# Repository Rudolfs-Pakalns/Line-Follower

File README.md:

# Line Follower

## This project contains code and resources for a line-following robot.

## Contents
- STM32 code for line-following robot
- KiCad schematic and PCB design files
- 3D model of the robot chassis
- Bill of Materials (BOM) for components used

[Line Follower Rules](https://robotuskola.lv/wp-content/uploads/2025/10/linefollower-rules-lv.pdf)

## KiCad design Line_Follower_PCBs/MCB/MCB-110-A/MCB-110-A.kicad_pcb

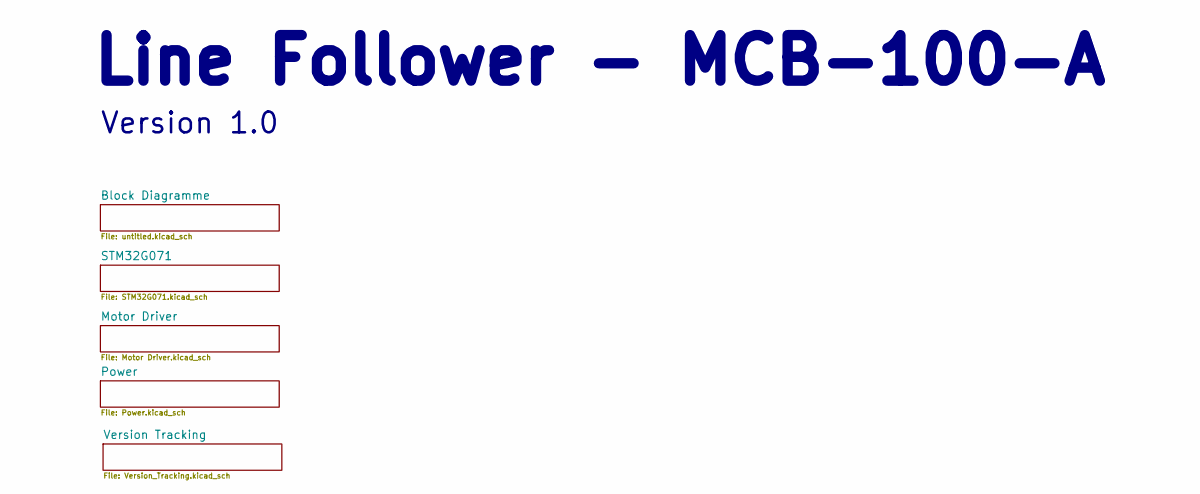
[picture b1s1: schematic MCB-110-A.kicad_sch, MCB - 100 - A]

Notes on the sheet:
Line Follower - MCB-100-A
Version 1.0

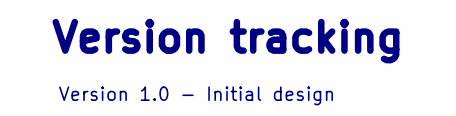
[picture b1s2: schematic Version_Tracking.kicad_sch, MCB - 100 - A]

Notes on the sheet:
Version 1.0 - Initial design
Version tracking

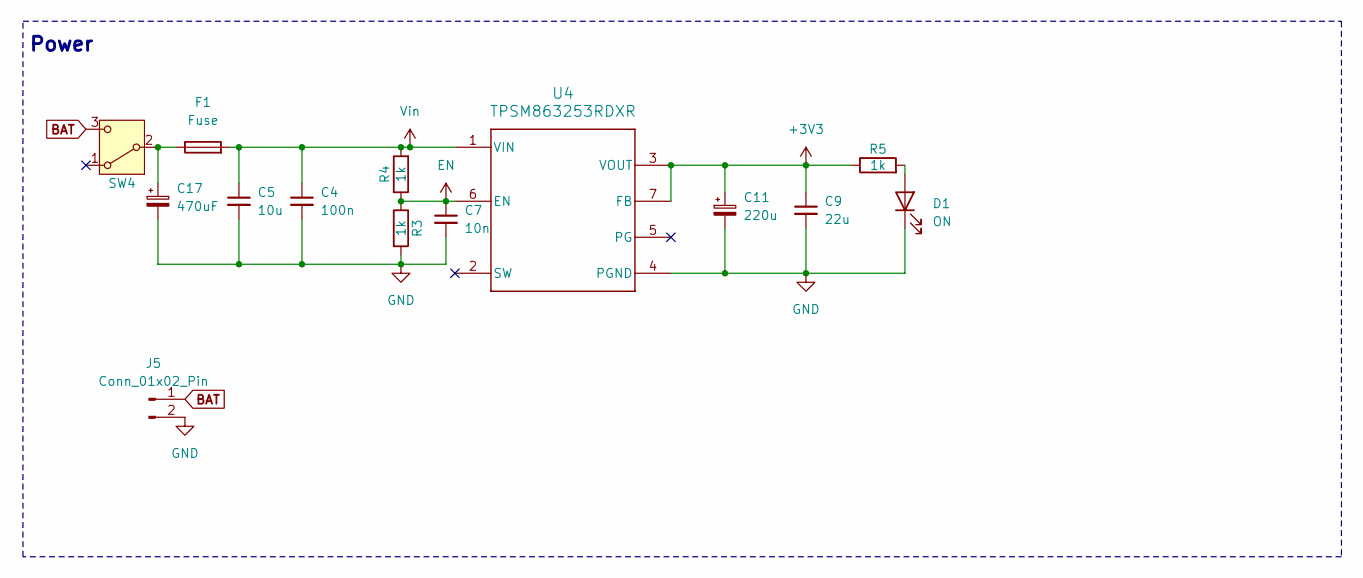
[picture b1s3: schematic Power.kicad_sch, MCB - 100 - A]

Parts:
C4: 100n; C_0805_2012Metric_Pad1.18x1.45mm_HandSolder
C5: 10u; C_0805_2012Metric_Pad1.18x1.45mm_HandSolder
C7: 10n; C_0805_2012Metric_Pad1.18x1.45mm_HandSolder
C9: 22u; C_0805_2012Metric_Pad1.18x1.45mm_HandSolder
C11: 220u; CP_Elec_8x10.5
C17: 470uF; CP_Elec_8x10.5
D1: ON; LED_1206_3216Metric
F1: Fuse; Fuse_Bourns_MF-RG300
J5: Conn_01x02_Pin; PinHeader_1x02_P2.54mm_Vertical
R3, R4, R5: 1k; R_0805_2012Metric_Pad1.20x1.40mm_HandSolder
SW4: SW_Nidec_CAS-120A1; SW_Slide_SPDT_Straight_CK_OS102011MS2Q
U4: TPSM863253RDXR; RDX0007A-MFG

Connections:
+3V3: C9.1, C11.1, R5.1, U4.3 (VOUT), U4.7 (FB); also elsewhere on the board
BAT: J5.1, SW4.3 (A); also elsewhere on the board
EN: C7.1, R3.1, R4.1, U4.6 (EN)
GND: C4.2, C5.2, C7.2, C9.2, C11.2, C17.2, D1.1 (K), J5.2, R3.2, U4.4 (PGND); also elsewhere on the board
unnamed: D1.2 (A), R5.2
unnamed: C17.1, F1.1, SW4.2 (B)
Vin: C4.1, C5.1, F1.2, R4.2, U4.1 (VIN)

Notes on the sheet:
Power

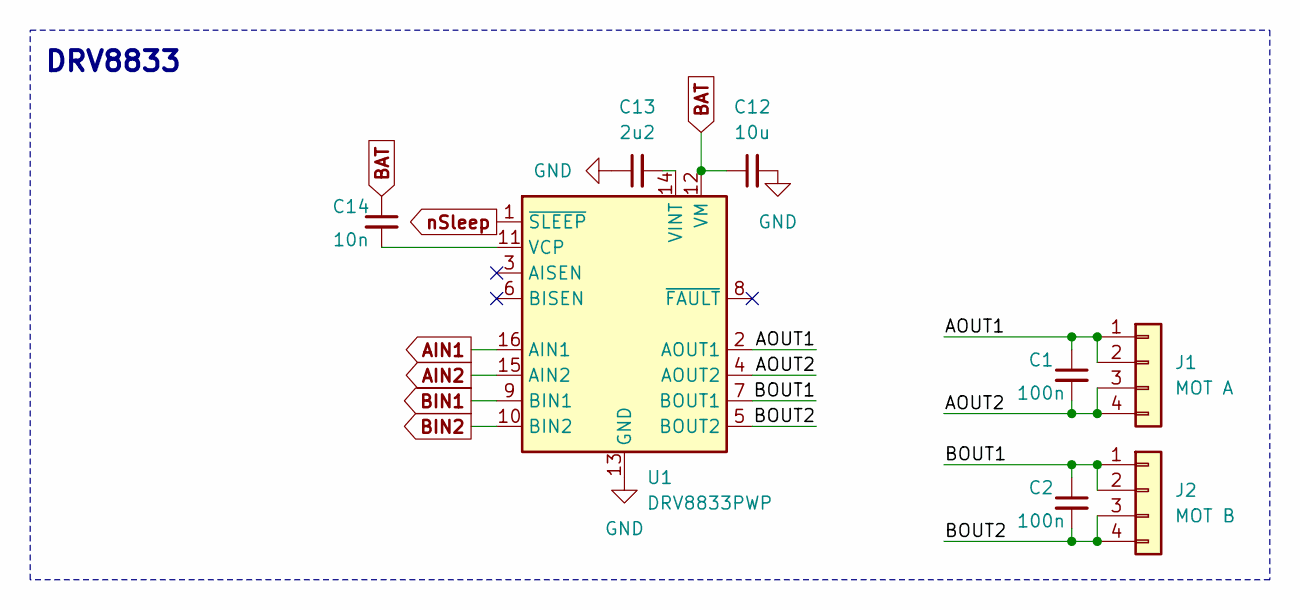
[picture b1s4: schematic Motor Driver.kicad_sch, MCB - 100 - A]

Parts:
C1, C2: 100n; C_0805_2012Metric_Pad1.18x1.45mm_HandSolder
C12: 10u; C_0805_2012Metric_Pad1.18x1.45mm_HandSolder
C13: 2u2; C_0805_2012Metric_Pad1.18x1.45mm_HandSolder
C14: 10n; C_0805_2012Metric_Pad1.18x1.45mm_HandSolder
J1: MOT A; PinHeader_1x04_P2.54mm_Vertical
J2: MOT B; PinHeader_1x04_P2.54mm_Vertical
U1: DRV8833PWP; HTSSOP-16-1EP_4.4x5mm_P0.65mm_EP3.4x5mm_Mask2.46x2.31mm_The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

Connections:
/Motor Driver/AOUT1: C1.1, J1.1, J1.2, U1.2 (AOUT1)
/Motor Driver/AOUT2: C1.2, J1.3, J1.4, U1.4 (AOUT2)
/Motor Driver/BOUT1: C2.1, J2.1, J2.2, U1.7 (BOUT1)
/Motor Driver/BOUT2: C2.2, J2.3, J2.4, U1.5 (BOUT2)
AIN1: U1.16 (AIN1); also elsewhere on the board
AIN2: U1.15 (AIN2); also elsewhere on the board
BAT: C12.1, C14.1, U1.12 (VM); also elsewhere on the board
BIN1: U1.9 (BIN1); also elsewhere on the board
BIN2: U1.10 (BIN2); also elsewhere on the board
GND: C12.2, C13.1, U1.13 (GND), U1.17 (GND); also elsewhere on the board
unnamed: C14.2, U1.11 (VCP)
unnamed: C13.2, U1.14 (VINT)
nSleep: U1.1 (~SLEEP); also elsewhere on the board

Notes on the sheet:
DRV8833

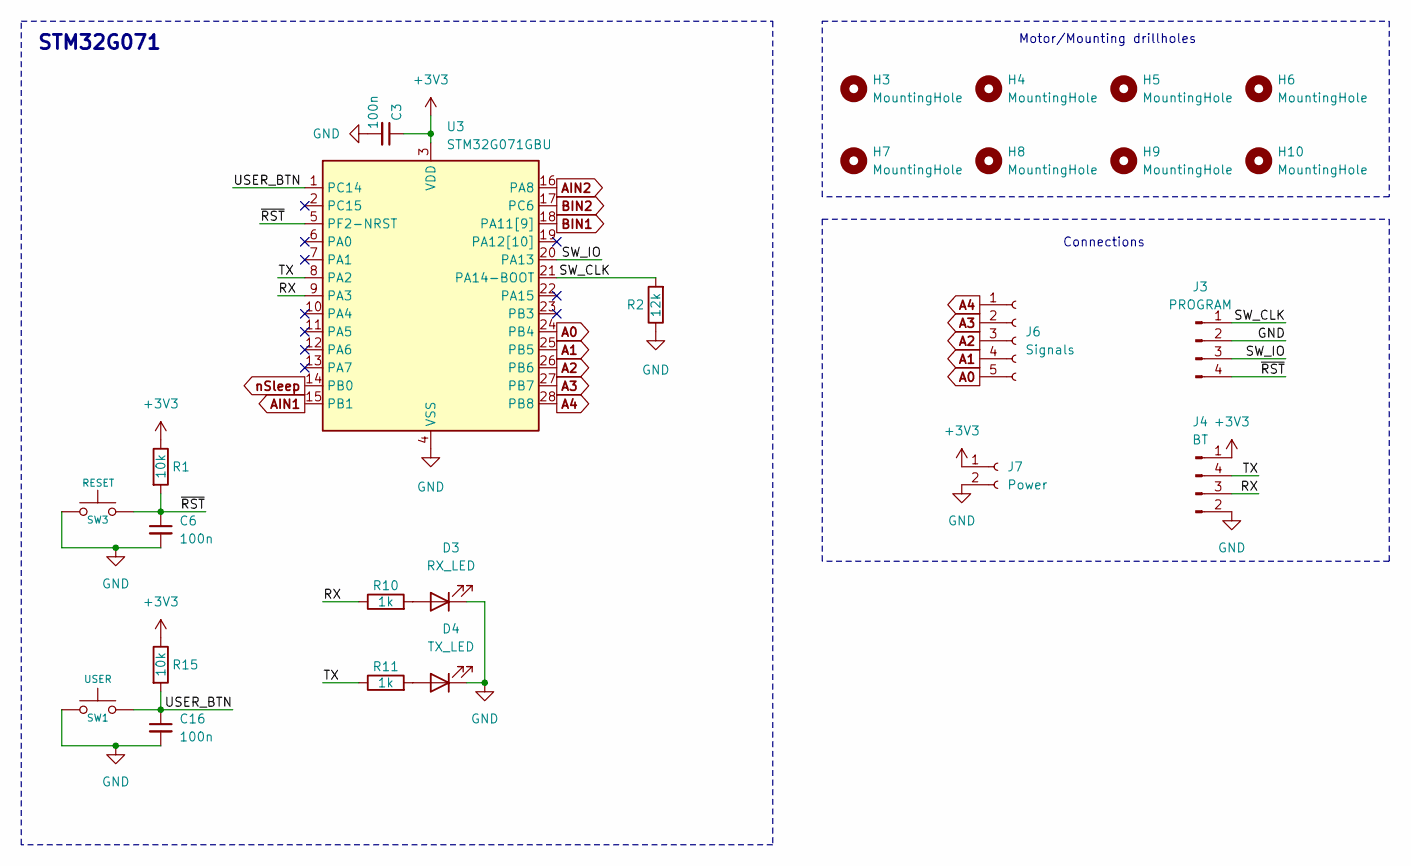
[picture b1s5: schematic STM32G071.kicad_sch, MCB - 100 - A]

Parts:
C3, C6, C16: 100n; C_0805_2012Metric_Pad1.18x1.45mm_HandSolder
D3: RX_LED; LED_1206_3216Metric
D4: TX_LED; LED_1206_3216Metric
H3, H4, H5, H6, H7, H8, H9, H10: MountingHole; MountingHole_3.2mm_M3
J3: PROGRAM; PinHeader_1x04_P2.54mm_Vertical
J4: BT; PinHeader_1x04_P2.54mm_Vertical
J6: Signals; JST_XH_B5B-XH-A_1x05_P2.50mm_Vertical
J7: Power; JST_XH_B2B-XH-A_1x02_P2.50mm_Vertical
R1, R15: 10k; R_0805_2012Metric_Pad1.20x1.40mm_HandSolder
R2: 12k; R_0805_2012Metric_Pad1.20x1.40mm_HandSolder
R10, R11: 1k; R_0805_2012Metric_Pad1.20x1.40mm_HandSolder
SW1: USER; SW_SPST_TL3305A
SW3: RESET; SW_SPST_TL3305A
U3: STM32G071GBU; QFN-28_4x4mm_P0.5mm

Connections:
+3V3: C3.1, J4.1, J7.1, R1.1, R15.1, U3.3 (VDD); also elsewhere on the board
/STM32G071/RX: J4.3, R10.1, U3.9 (PA3)
/STM32G071/SW_CLK: J3.1, R2.2, U3.21 (PA14-BOOT)
/STM32G071/SW_IO: J3.3, U3.20 (PA13)
/STM32G071/TX: J4.4, R11.1, U3.8 (PA2)
/STM32G071/USER_BTN: C16.1, R15.2, SW1.2, U3.1 (PC14)
/STM32G071/~RST: C6.1, J3.4 (Pin_2), R1.2, SW3.2, U3.5 (PF2-NRST)
A0: J6.5, U3.24 (PB4)
A1: J6.4, U3.25 (PB5)
A2: J6.3, U3.26 (PB6)
A3: J6.2, U3.27 (PB7)
A4: J6.1, U3.28 (PB8)
AIN1: U3.15 (PB1); also elsewhere on the board
AIN2: U3.16 (PA8); also elsewhere on the board
BIN1: U3.18 (PA11[9]); also elsewhere on the board
BIN2: U3.17 (PC6); also elsewhere on the board
GND: C3.2, C6.2, C16.2, D3.1 (K), D4.1 (K), J3.2 (Pin_4), J4.2, J7.2, R2.1, SW1.1, SW3.1, U3.4 (VSS); also elsewhere on the board
unnamed: D3.2 (A), R10.2
unnamed: D4.2 (A), R11.2
nSleep: U3.14 (PB0); also elsewhere on the board

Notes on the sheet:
Motor/Mounting drillholes
Connections
STM32G071

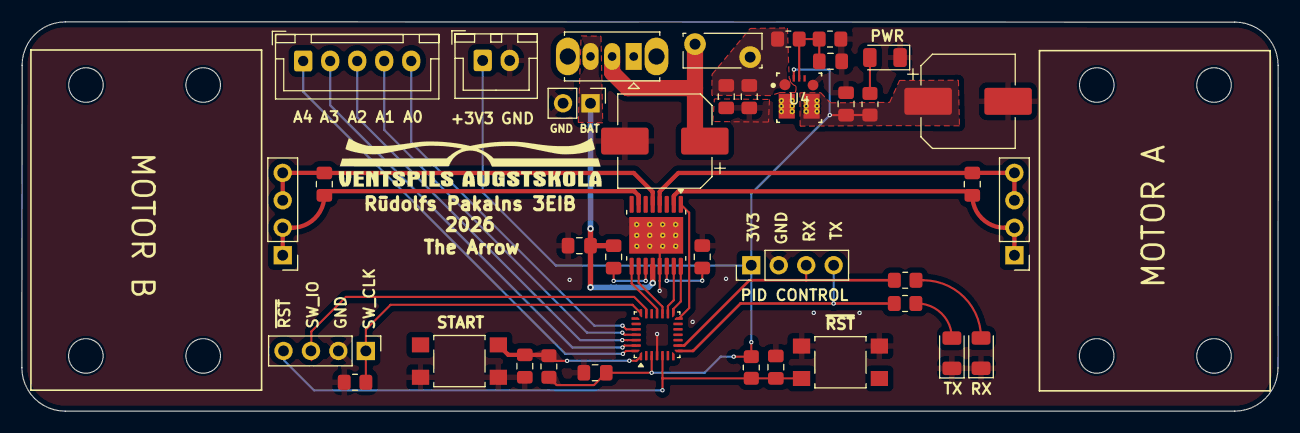
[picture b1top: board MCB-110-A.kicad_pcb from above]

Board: 2 copper layers, 116.2 x 36.0 mm, 47 parts (0 on the bottom side), 31 nets.

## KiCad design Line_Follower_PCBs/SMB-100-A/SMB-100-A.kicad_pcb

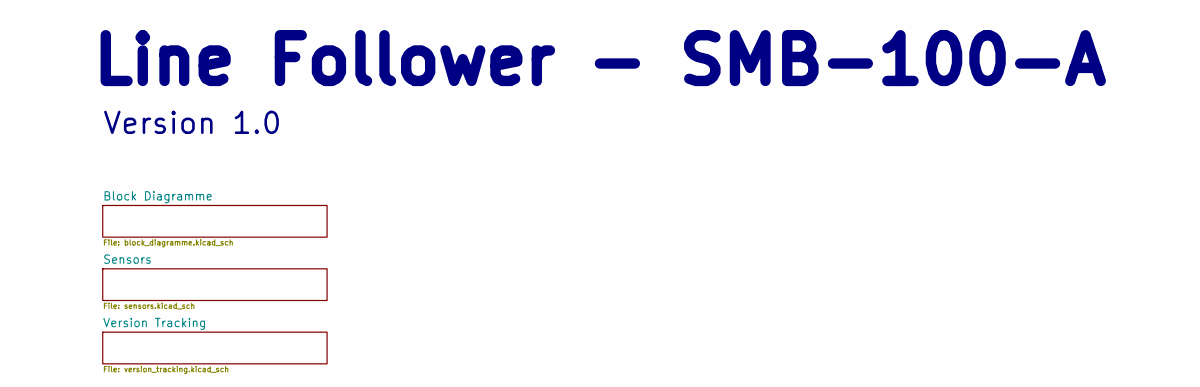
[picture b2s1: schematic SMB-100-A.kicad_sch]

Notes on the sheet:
Version 1.0
Line Follower - SMB-100-A

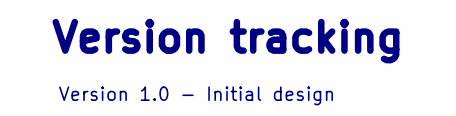
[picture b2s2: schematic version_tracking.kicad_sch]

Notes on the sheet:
Version 1.0 - Initial design
Version tracking

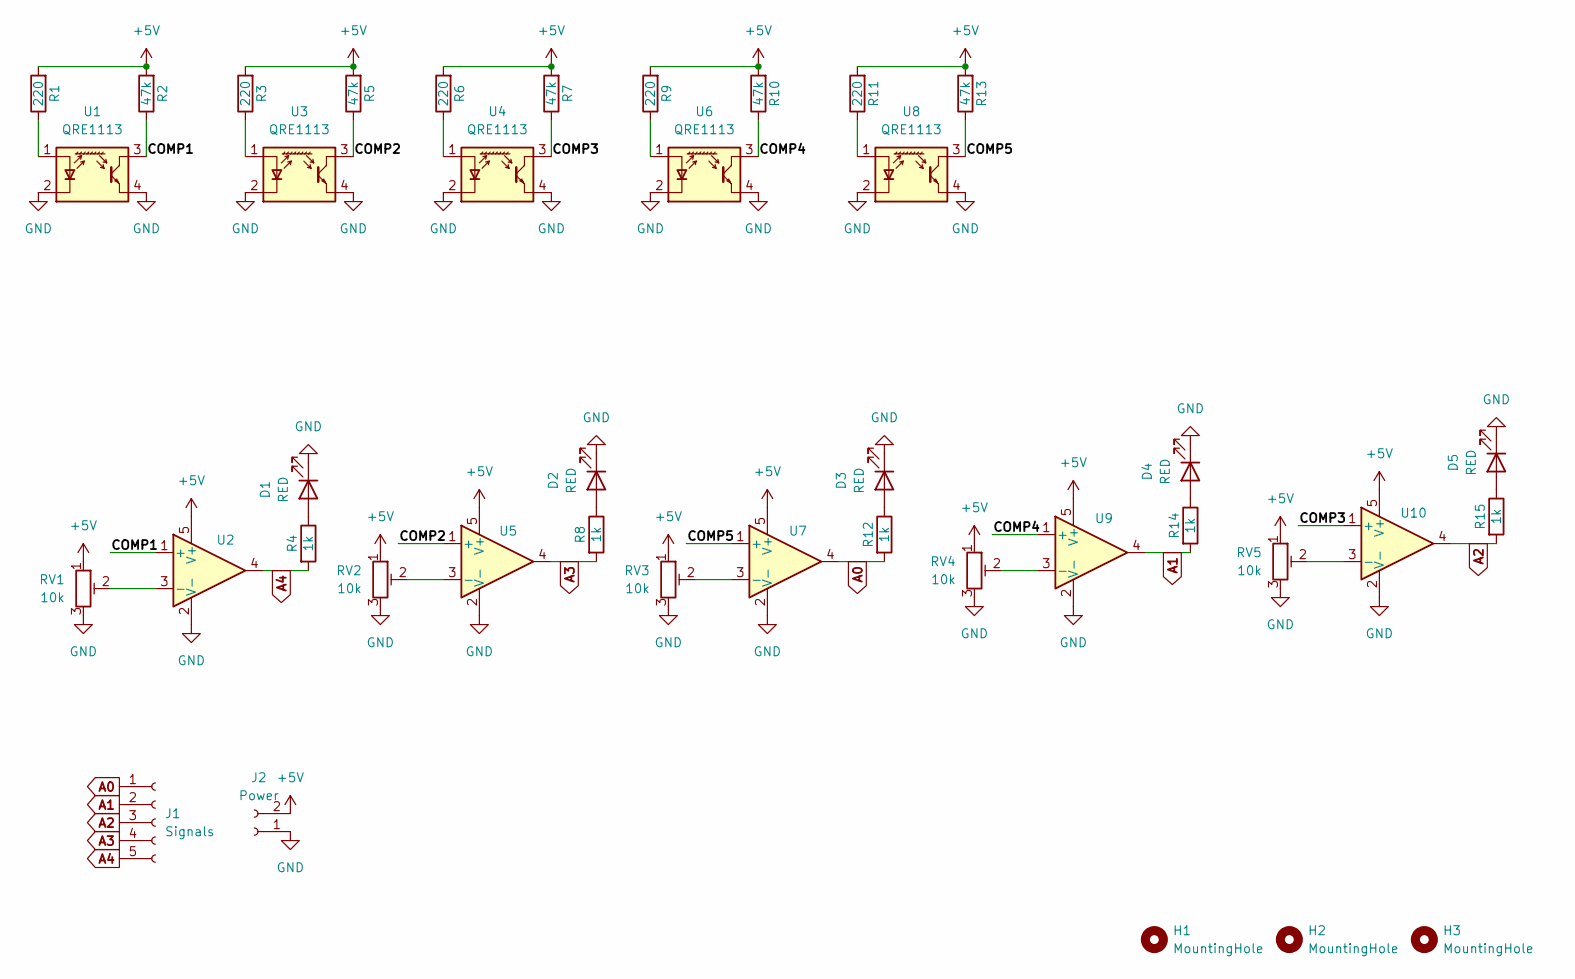
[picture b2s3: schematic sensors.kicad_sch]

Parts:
D1, D2, D3, D4, D5: RED; LED_1206_3216Metric
H1, H2, H3: MountingHole; MountingHole_3.2mm_M3
J1: Signals; JST_XH_B5B-XH-A_1x05_P2.50mm_Vertical
J2: Power; JST_XH_B2B-XH-A_1x02_P2.50mm_Vertical
R1, R3, R6, R9, R11: 220; R_0805_2012Metric_Pad1.20x1.40mm_HandSolder
R2, R5, R7, R10, R13: 47k; R_0805_2012Metric_Pad1.20x1.40mm_HandSolder
R4, R8, R12, R14, R15: 1k; R_0805_2012Metric_Pad1.20x1.40mm_HandSolder
RV1, RV2, RV3, RV4, RV5: 10k; Potentiometer_Bourns_TC33X_Vertical
U1, U3, U4, U6, U8: QRE1113; OnSemi_CASE100AQ
U2, U5, U7, U9, U10: MCP6001U; SOT-23-5_HandSoldering

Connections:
+3V3: J2.2, R1.2, R2.2, R3.2, R5.2, R6.2, R7.2, R9.2, R10.2, R11.2, R13.2, RV1.1, RV2.1, RV3.1, RV4.1, RV5.1, U2.5 (V+), U5.5 (V+), U7.5 (V+), U9.5 (V+), U10.5 (V+)
/Sensors/COMP1: R2.1, U1.3, U2.1 (+)
/Sensors/COMP2: R5.1, U3.3, U5.1 (+)
/Sensors/COMP3: R7.1, U4.3, U10.1 (+)
/Sensors/COMP4: R10.1, U6.3, U9.1 (+)
/Sensors/COMP5: R13.1, U7.1 (+), U8.3
A0: J1.1, R12.2, U7.4
A1: J1.2, R14.2, U9.4
A2: J1.3, R15.2, U10.4
A3: J1.4, R8.2, U5.4
A4: J1.5, R4.2, U2.4
GND: D1.1 (K), D2.1 (K), D3.1 (K), D4.1 (K), D5.1 (K), J2.1, RV1.3, RV2.3, RV3.3, RV4.3, RV5.3, U1.2 (K), U1.4, U2.2 (V-), U3.2 (K), U3.4, U4.2 (K), U4.4, U5.2 (V-), U6.2 (K), U6.4, U7.2 (V-), U8.2 (K), U8.4, U9.2 (V-), U10.2 (V-)
unnamed: D1.2 (A), R4.1
unnamed: D2.2 (A), R8.1
unnamed: D3.2 (A), R12.1
unnamed: D4.2 (A), R14.1
unnamed: D5.2 (A), R15.1
unnamed: R1.1, U1.1 (A)
unnamed: RV1.2, U2.3 (-)
unnamed: R3.1, U3.1 (A)
unnamed: R6.1, U4.1 (A)
unnamed: RV2.2, U5.3 (-)
unnamed: R9.1, U6.1 (A)
unnamed: RV3.2, U7.3 (-)
unnamed: R11.1, U8.1 (A)
unnamed: RV4.2, U9.3 (-)
unnamed: RV5.2, U10.3 (-)

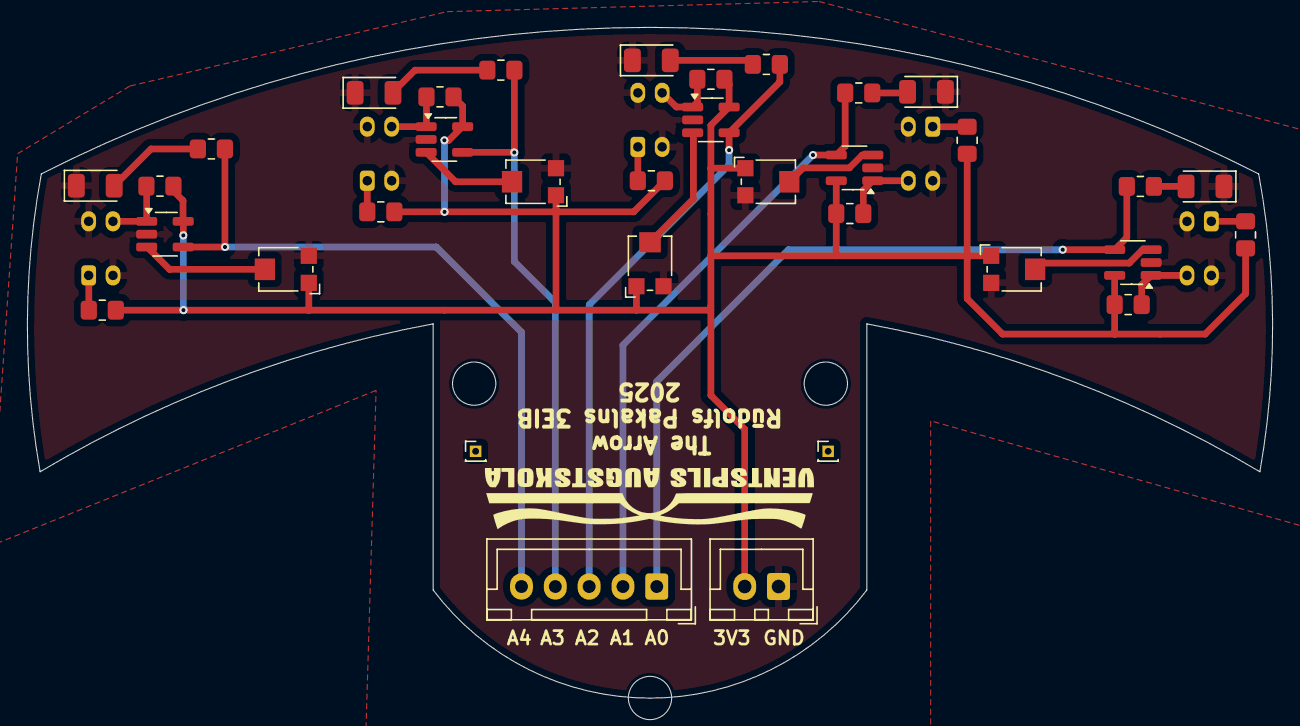
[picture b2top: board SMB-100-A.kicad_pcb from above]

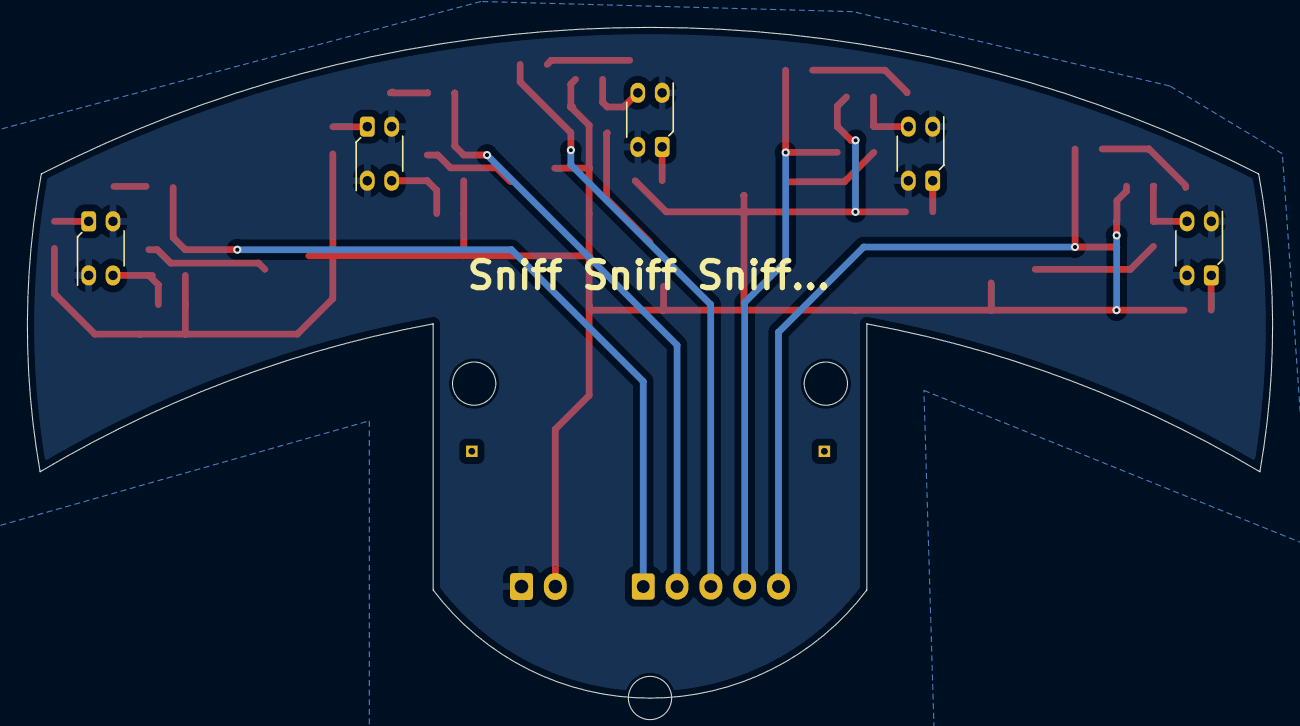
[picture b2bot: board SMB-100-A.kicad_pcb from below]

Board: 2 copper layers, 92.1 x 49.6 mm, 42 parts (5 on the bottom side), 27 nets.

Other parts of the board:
J3, J4: Conn_01x01_Pin; PinHeader_1x01_P1.00mm_Vertical

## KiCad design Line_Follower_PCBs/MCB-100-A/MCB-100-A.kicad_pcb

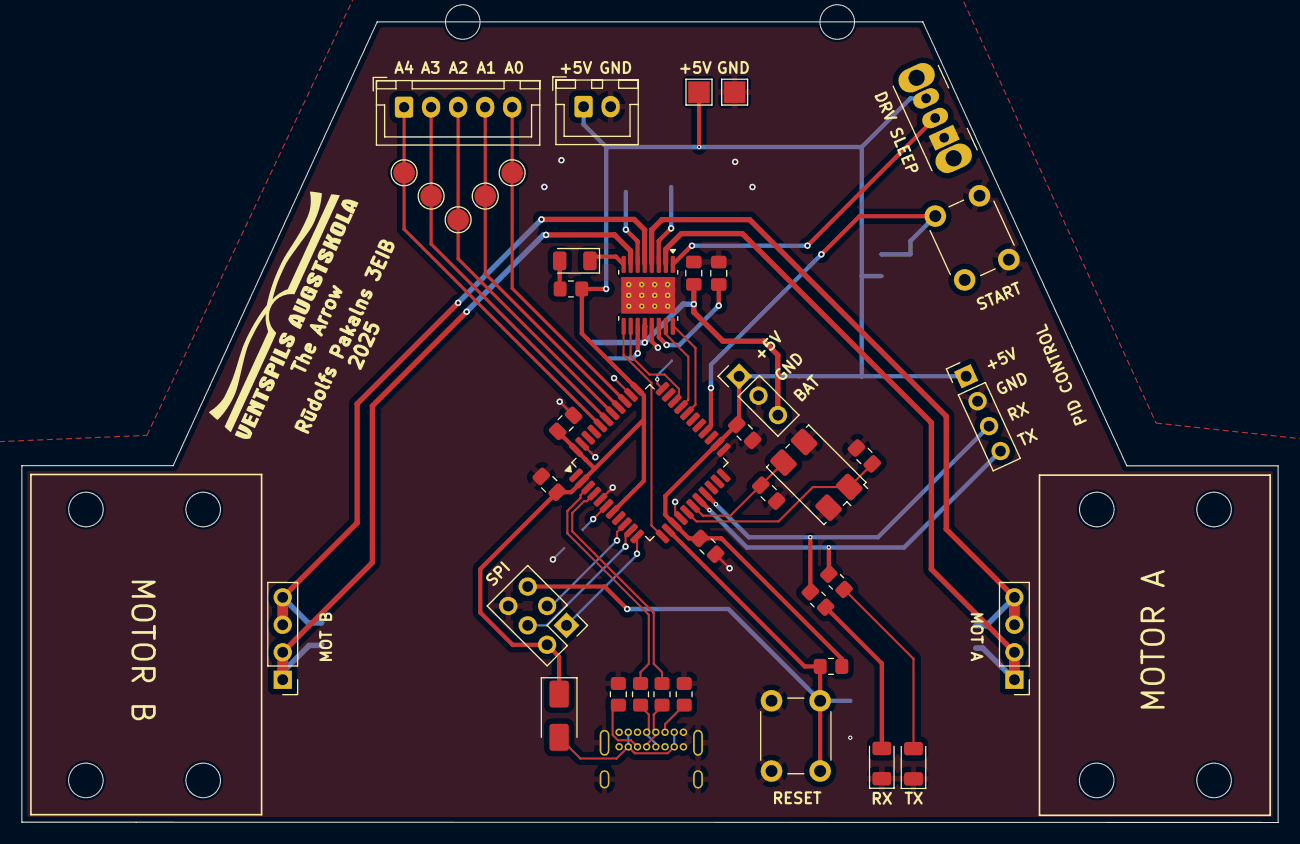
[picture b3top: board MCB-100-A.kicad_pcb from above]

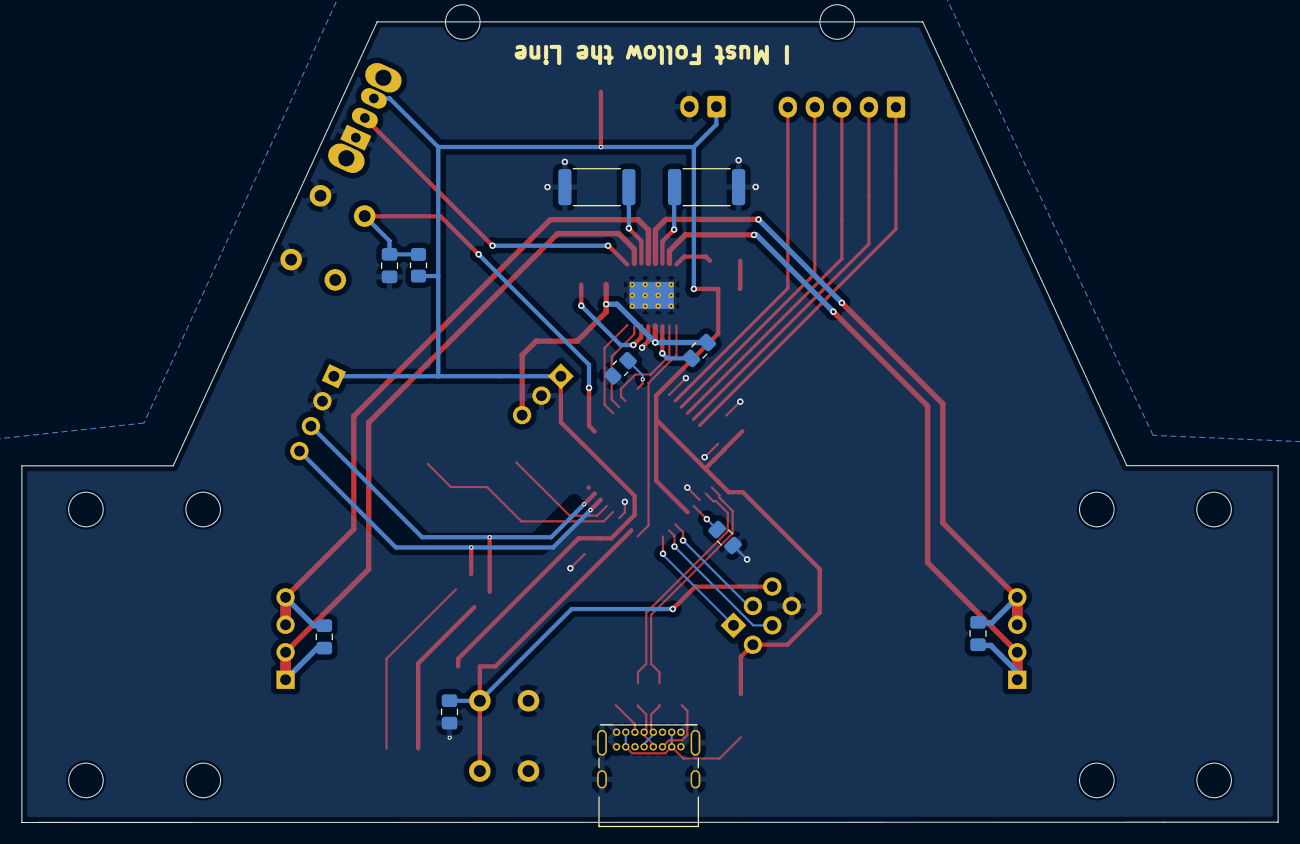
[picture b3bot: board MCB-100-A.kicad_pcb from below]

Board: 2 copper layers, 116.2 x 74.1 mm, 61 parts (11 on the bottom side), 43 nets.

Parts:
A1, A2, A3, A4, A5: TestPoint; TestPoint_Pad_D2.0mm
C1, C1#2, C2, C2#2, C3, C6, C15, C16: 100n; C_0805_2012Metric_Pad1.18x1.45mm_HandSolder
C4, C5: 20p; C_0805_2012Metric_Pad1.18x1.45mm_HandSolder
C7: 1u; C_0805_2012Metric_Pad1.18x1.45mm_HandSolder
C12: 10u; C_0805_2012Metric_Pad1.18x1.45mm_HandSolder
C13: 2u2; C_0805_2012Metric_Pad1.18x1.45mm_HandSolder
C14: 10n; C_0805_2012Metric_Pad1.18x1.45mm_HandSolder
D3: RX_LED; LED_1206_3216Metric
D4: TX_LED; LED_1206_3216Metric
D5: FAULT; LED_1206_3216Metric
D12: D_Schottky; D_SMA
H1, H2, H3, H4, H5, H6, H7, H8, H9, H10: MountingHole; MountingHole_3.2mm_M3
J1: MOT A; PinHeader_1x04_P2.54mm_Vertical
J2: MOT B; PinHeader_1x04_P2.54mm_Vertical
J3: USB_C_Receptacle_USB2.0_16P; USB_C_Receptacle_GCT_USB4085
J4: BT; PinHeader_1x04_P2.54mm_Vertical
J6: Signals; JST_XH_B5B-XH-A_1x05_P2.50mm_Vertical
J7: Power; JST_XH_B2B-XH-A_1x02_P2.50mm_Vertical
J9: Conn_01x03_Pin; PinHeader_1x03_P2.54mm_Vertical
J14: SPI; PinHeader_2x03_P2.54mm_Vertical
R1, R4, R15: 10k; R_0805_2012Metric_Pad1.20x1.40mm_HandSolder
R2, R3: 22; R_0805_2012Metric_Pad1.20x1.40mm_HandSolder
R10, R11, R12: 1k; R_0805_2012Metric_Pad1.20x1.40mm_HandSolder
R13, R14: 0.2; R_2512_6332Metric
R31, R32: 5k1; R_0805_2012Metric_Pad1.20x1.40mm_HandSolder
SW1: USER; SW_PUSH_6mm_H4.3mm
SW2: Sl_En; SW_Slide_SPDT_Angled_CK_OS102011MA1Q
SW3: RESET; SW_PUSH_6mm_H4.3mm
TP9, TP10: TestPoint; TestPoint_Pad_2.0x2.0mm
U1: DRV8833PWP; HTSSOP-16-1EP_4.4x5mm_P0.65mm_EP3.4x5mm_Mask2.46x2.31mm_The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
U2: ATmega32U4-A; TQFP-44_10x10mm_P0.8mm
Y1: Crystal_GND24; Crystal_SMD_FOX_FQ7050-4Pin_7.0x5.0mm

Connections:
+5V: C1.1, C2.1, C3.1, C15.1, D12.1 (K), J4.1, J7.1, J9.1, J14.2, R1.1, R12.2, R15.1, SW2.3 (A), TP9.1, U2.2 (UVCC), U2.7 (VBUS), U2.14 (VCC), U2.24 (AVCC), U2.34 (VCC), U2.44 (AVCC)
/ATmega32u4/D1+: J3.A6 (D+), J3.B6 (D+), R2.2
/ATmega32u4/D1-: J3.A7 (D-), J3.B7 (D-), R3.1
/ATmega32u4/D+: R2.1, U2.4 (D+)
/ATmega32u4/D-: R3.2, U2.3 (D-)
/ATmega32u4/MISO: J14.1, U2.11 (PB3)
/ATmega32u4/MOSI: J14.4, U2.10 (PB2)
/ATmega32u4/RESET: C6.1, J14.5, R1.2, SW3.2, U2.13 (~RESET)
/ATmega32u4/RX: J4.3, R10.1, U2.19 (PD1)
/ATmega32u4/SCK: J14.3, U2.9 (PB1)
/ATmega32u4/TX: J4.4, R11.1, U2.18 (PD0)
/ATmega32u4/USER_BTN: C16.1, R15.2, SW1.2, U2.26 (PD6)
/ATmega32u4/XTAL1: C5.1, U2.17 (XTAL1), Y1.3
/ATmega32u4/XTAL2: C4.1, U2.16 (XTAL2), Y1.1
/Motor Driver/AOUT1: C1#2.1, J1.1, J1.2, U1.2 (AOUT1)
/Motor Driver/AOUT2: C1#2.2, J1.3, J1.4, U1.4 (AOUT2)
/Motor Driver/ASEN: R13.1, U1.3 (AISEN)
/Motor Driver/BOUT1: C2#2.1, J2.1, J2.2, U1.7 (BOUT1)
/Motor Driver/BOUT2: C2#2.2, J2.3, J2.4, U1.5 (BOUT2)
/Motor Driver/BSEN: R14.1, U1.6 (BISEN)
/Motor Driver/Sleep: SW2.2 (B), U1.1 (~SLEEP)
A0: A4.1, J6.5, U2.36 (PF7)
A1: A3.1, J6.4, U2.37 (PF6)
A2: A5.1, J6.3, U2.38 (PF5)
A3: A2.1, J6.2, U2.39 (PF4)
A4: A1.1, J6.1, U2.40 (PF1)
BAT: C12.1, C14.1, J9.3, U1.12 (VM)
D5: U1.10 (BIN2), U2.31 (PC6)
D9: U1.16 (AIN1), U2.29 (PB5)
D10: U1.15 (AIN2), U2.30 (PB6)
D11: U1.9 (BIN1), U2.12 (PB7)
GND: C1.2, C2.2, C3.2, C4.2, C5.2, C6.2, C7.2, C12.2, C13.1, C15.2, C16.2, D3.1 (K), D4.1 (K), J3.A1 (GND), J3.A12 (GND), J3.B1 (GND), J3.B12 (GND), J3.S1 (SHIELD), J4.2, J7.2, J9.2, J14.6, R4.2, R13.2, R14.2, R31.2, R32.2, SW1.1, SW2.1 (C), SW3.1, TP10.1, U1.13 (GND), U1.17 (GND), U2.5 (UGND), U2.15 (GND), U2.23 (GND), U2.35 (GND), U2.43 (GND), Y1.2, Y1.4
unnamed: D3.2 (A), R10.2
unnamed: D4.2 (A), R11.2
unnamed: D5.2 (A), R12.1
unnamed: D5.1 (K), U1.8 (~FAULT)
unnamed: D12.2 (A), J3.A4 (VBUS), J3.A9 (VBUS), J3.B4 (VBUS), J3.B9 (VBUS)
unnamed: J3.A5 (CC1), R31.1
unnamed: J3.B5 (CC2), R32.1
unnamed: C14.2, U1.11 (VCP)
unnamed: C13.2, U1.14 (VINT)
unnamed: C7.1, U2.6 (UCAP)
unnamed: R4.1, U2.33 (~HWB/PE2)

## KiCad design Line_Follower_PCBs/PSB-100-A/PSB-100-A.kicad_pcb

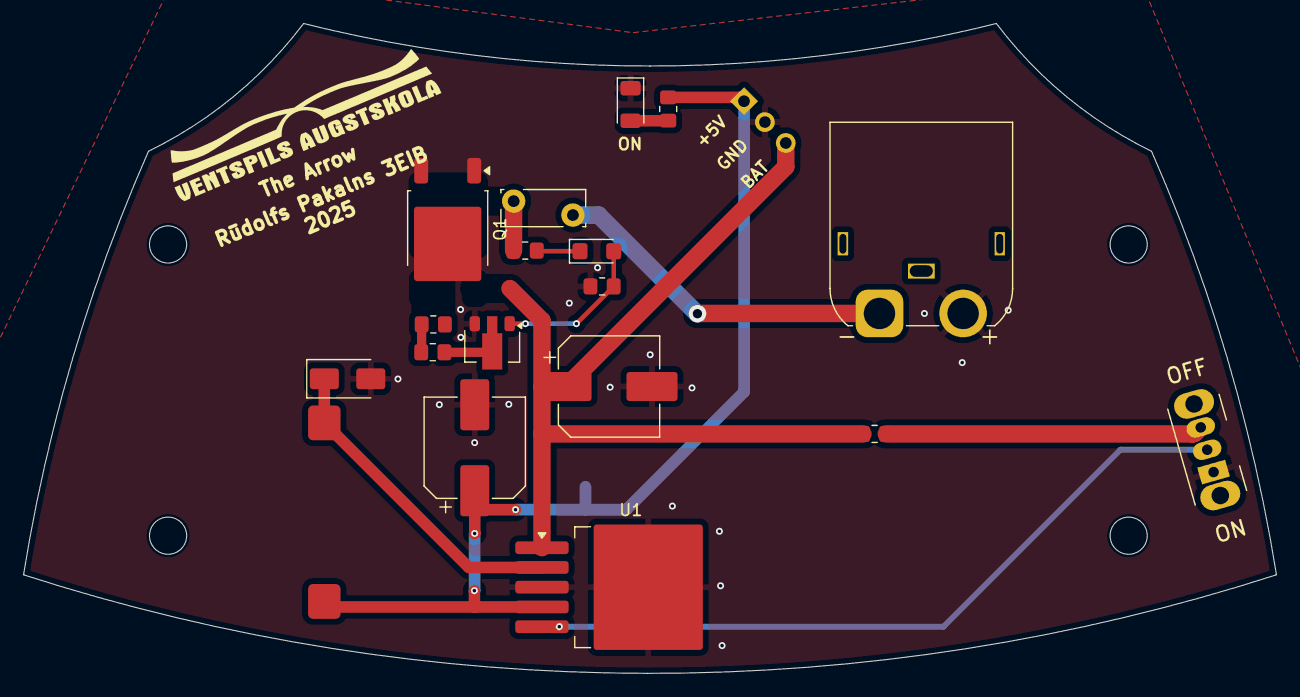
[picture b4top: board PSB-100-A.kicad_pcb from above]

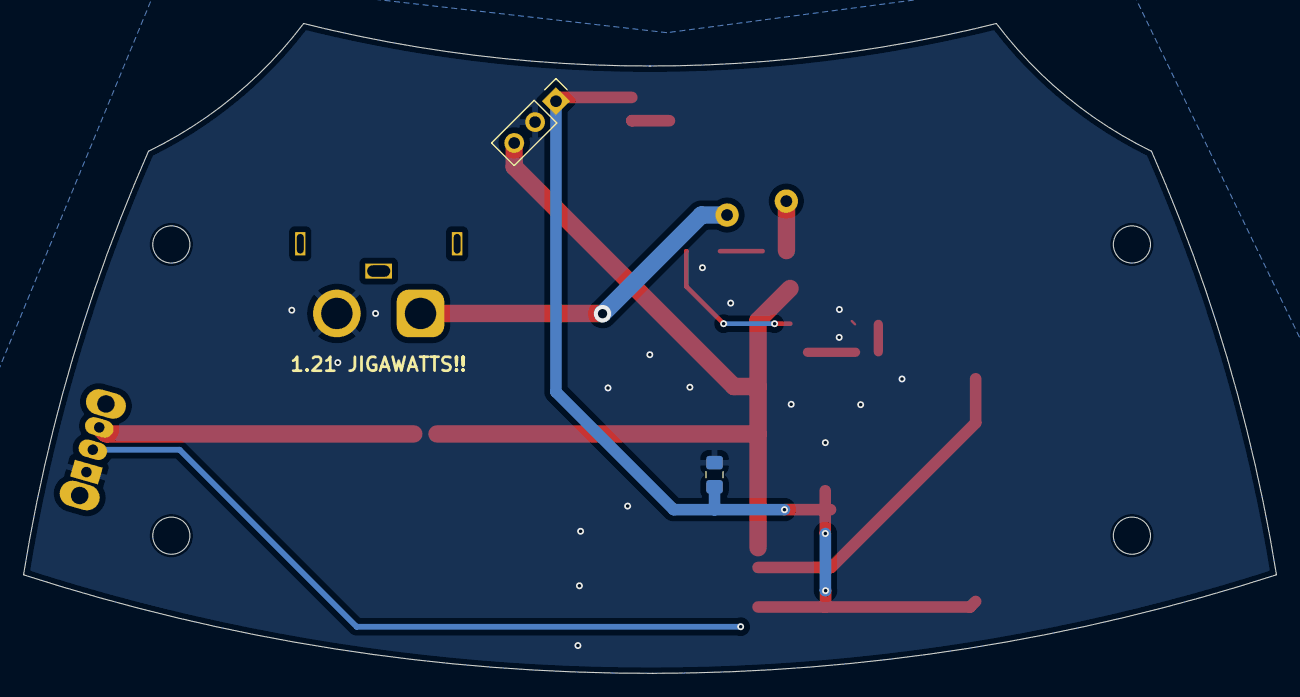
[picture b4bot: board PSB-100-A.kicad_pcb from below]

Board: 2 copper layers, 107.9 x 55.9 mm, 24 parts (2 on the bottom side), 13 nets.

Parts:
BT1: Battery; AMASS_XT60IPW-M_1x03_P7.20mm_Horizontal
C9: 100n; C_0805_2012Metric_Pad1.18x1.45mm_HandSolder
C11: 220u; CP_Elec_8x10.5
C17: 470uF; CP_Elec_8x10.5
D1: ON; LED_1206_3216Metric
D2: D_Zener; D_SMF
D11: D_Schottky; D_SMA
DO5022P1: 22hH; DO5022P
F1: Fuse; Fuse_Bourns_MF-RG300
H1, H2, H3, H4: MountingHole; MountingHole_3.2mm_M3
J8: Conn_01x03_Pin; PinHeader_1x03_P2.54mm_Vertical
Q1: SUD50P06-15; TO-252-2
Q2: BCX56; SOT-89-3
R5: 1k; R_0805_2012Metric_Pad1.20x1.40mm_HandSolder
R6: 130; R_0805_2012Metric_Pad1.20x1.40mm_HandSolder
R7: 220; R_0805_2012Metric_Pad1.20x1.40mm_HandSolder
R8: 400; R_0805_2012Metric_Pad1.20x1.40mm_HandSolder
R9, R33: 10k; R_0805_2012Metric_Pad1.20x1.40mm_HandSolder
SW4: SW_Nidec_CAS-120A1; SW_Slide_SPDT_Angled_CK_OS102011MA1Q
U1: LM2596S-5; TO-263-5_TabPin3

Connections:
+5V: C9.1, C11.1, DO5022P1.2, J8.1, R5.1, U1.4 (FB)
BAT: C17.1, J8.3, Q1.2 (D), R33.1, U1.1 (VIN)
GND: BT1.2 (-), C9.2, C11.2, C17.2, D1.1 (K), D11.2 (A), J8.2, Q2.3 (E), R8.1, SW4.1 (C), U1.3 (GND)
unnamed: BT1.1 (+), F1.1
unnamed: D1.2 (A), R5.2
unnamed: D2.2 (A), Q2.1 (B), R8.2
unnamed: D2.1 (K), R6.1
unnamed: D11.1 (K), DO5022P1.1, U1.2 (OUT)
unnamed: F1.2, R6.2, R9.2
unnamed: Q1.1 (G), R7.2, R9.1
unnamed: Q2.2 (C), R7.1
unnamed: R33.2, SW4.3 (A)
unnamed: SW4.2 (B), U1.5 (~ON/OFF)
